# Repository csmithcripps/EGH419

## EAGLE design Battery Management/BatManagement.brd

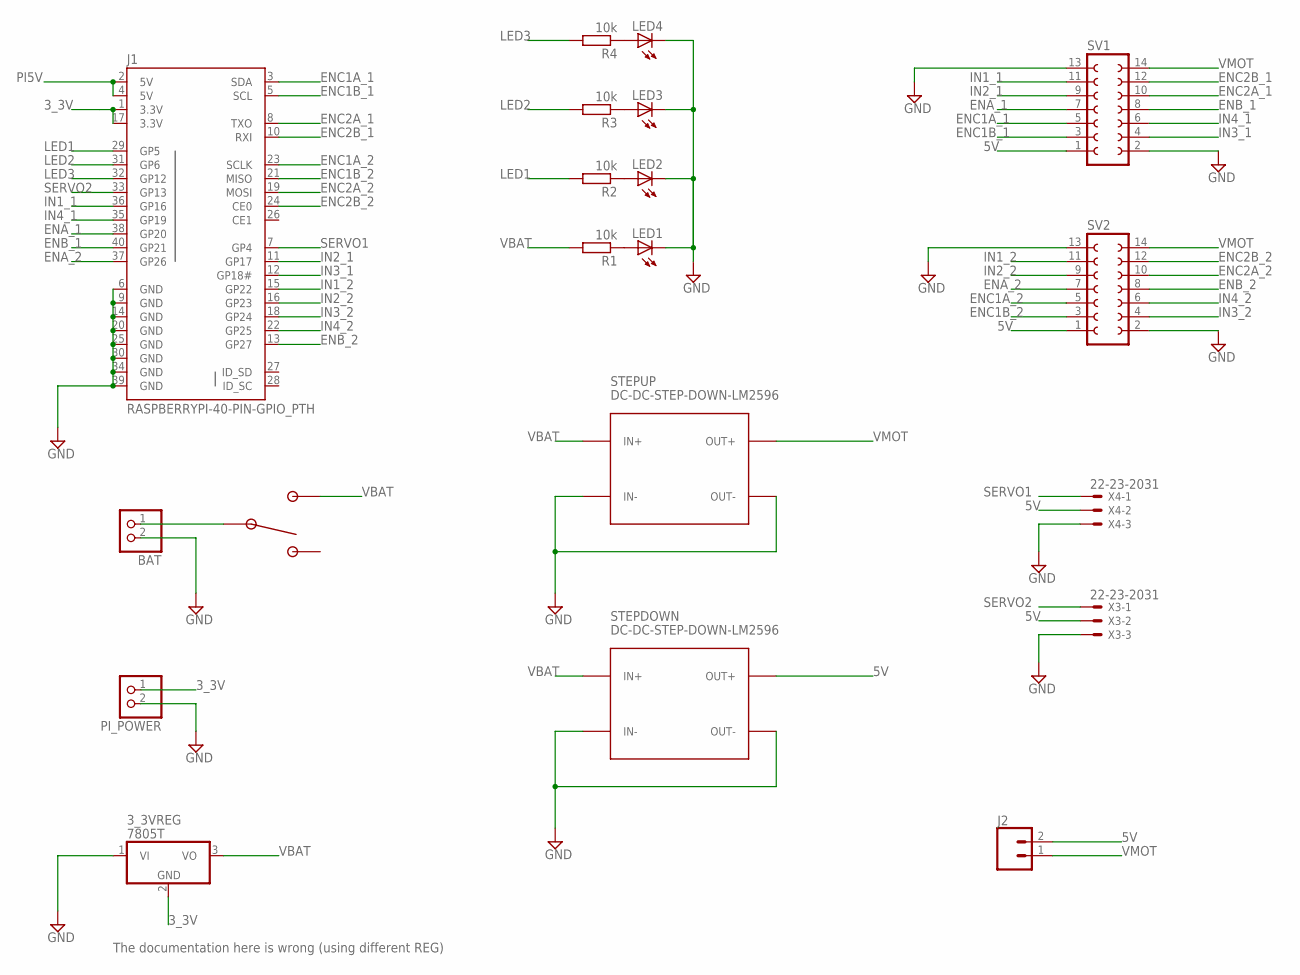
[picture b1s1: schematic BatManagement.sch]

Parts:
3_3VREG: 7805T; TO220H
BAT: JST_2PIN-THM; JST-PH-2-THM
J1: RASPBERRYPI-40-PIN-GPIO_PTH; 2X20_SHROUDED
J2: CONN_02; 1X02
LED1, LED2, LED3, LED4: LED5MM
PI_POWER: JST_2PIN-THM; JST-PH-2-THM
R1, R2, R3, R4: 10k; 0204/5
STEPDOWN: DC-DC-STEP-DOWN-LM2596
STEPUP: DC-DC-STEP-DOWN-LM2596
SV1, SV2: FE07-2
SW1: 100SP1T2B4M6QE; TOGGLE_RA
X3, X4: 22-23-2031

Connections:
3_3V: 3_3VREG.2 (GND), J1.1 (3.3V), J1.17 (3.3V), PI_POWER.1 (2)
5V: J2.2, STEPDOWN.OUT+, SV1.1, SV2.1, X3.2, X4.2
ENA_1: J1.38 (GP20), SV1.7
ENA_2: J1.37 (GP26), SV2.7
ENB_1: J1.40 (GP21), SV1.8
ENB_2: J1.13 (GP27), SV2.8
ENC1A_1: J1.3 (SDA), SV1.5
ENC1A_2: J1.23 (SCLK), SV2.5
ENC1B_1: J1.5 (SCL), SV1.3
ENC1B_2: J1.21 (MISO), SV2.3
ENC2A_1: J1.8 (TXO), SV1.10
ENC2A_2: J1.19 (MOSI), SV2.10
ENC2B_1: J1.10 (RXI), SV1.12
ENC2B_2: J1.24 (CE0), SV2.12
GND: 3_3VREG.1 (VI), BAT.2 (1), J1.6 (GND), J1.9 (GND), J1.14 (GND), J1.20 (GND), J1.25 (GND), J1.30 (GND), J1.34 (GND), J1.39 (GND), LED1.K (C), LED2.K (C), LED3.K (C), LED4.K (C), PI_POWER.2 (1), STEPDOWN.IN-, STEPDOWN.OUT-, STEPUP.IN-, STEPUP.OUT-, SV1.2, SV1.13, SV2.2, SV2.13, X3.3, X4.3
IN1_1: J1.36 (GP16), SV1.11
IN1_2: J1.15 (GP22), SV2.11
IN2_1: J1.11 (GP17), SV1.9
IN2_2: J1.16 (GP23), SV2.9
IN3_1: J1.12 (GP18#), SV1.4
IN3_2: J1.18 (GP24), SV2.4
IN4_1: J1.35 (GP19), SV1.6
IN4_2: J1.22 (GP25), SV2.6
LED1: J1.29 (GP5), R2.2
LED2: J1.31 (GP6), R3.2
LED3: J1.32 (GP12), R4.2
unnamed: LED1.A, R1.1
unnamed: LED2.A, R2.1
unnamed: LED3.A, R3.1
unnamed: LED4.A, R4.1
unnamed: BAT.1 (2), SW1.2 (COM)
PI5V: J1.2 (5V), J1.4 (5V)
SERVO1: J1.7 (GP4), X4.1
SERVO2: J1.33 (GP13), X3.1
VBAT: 3_3VREG.3 (VO), R1.2, STEPDOWN.IN+, STEPUP.IN+, SW1.1
VMOT: J2.1, STEPUP.OUT+, SV1.14, SV2.14

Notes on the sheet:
The documentation here is wrong (using different REG)

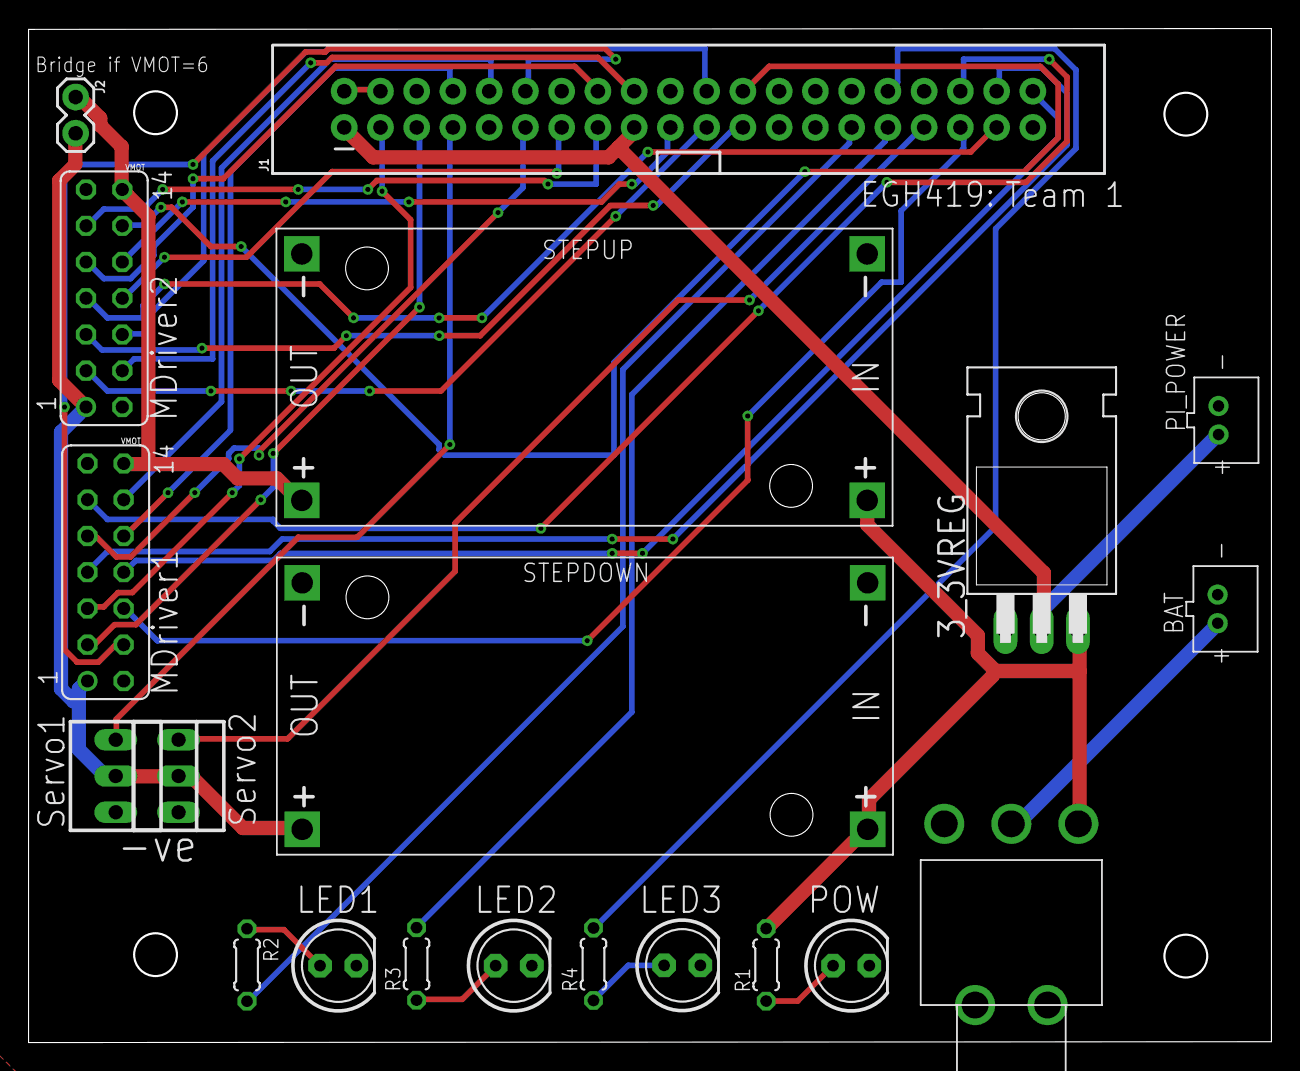
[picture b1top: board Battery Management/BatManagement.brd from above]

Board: 2 copper layers, 87.1 x 71.1 mm, 20 parts (0 on the bottom side), 36 nets.

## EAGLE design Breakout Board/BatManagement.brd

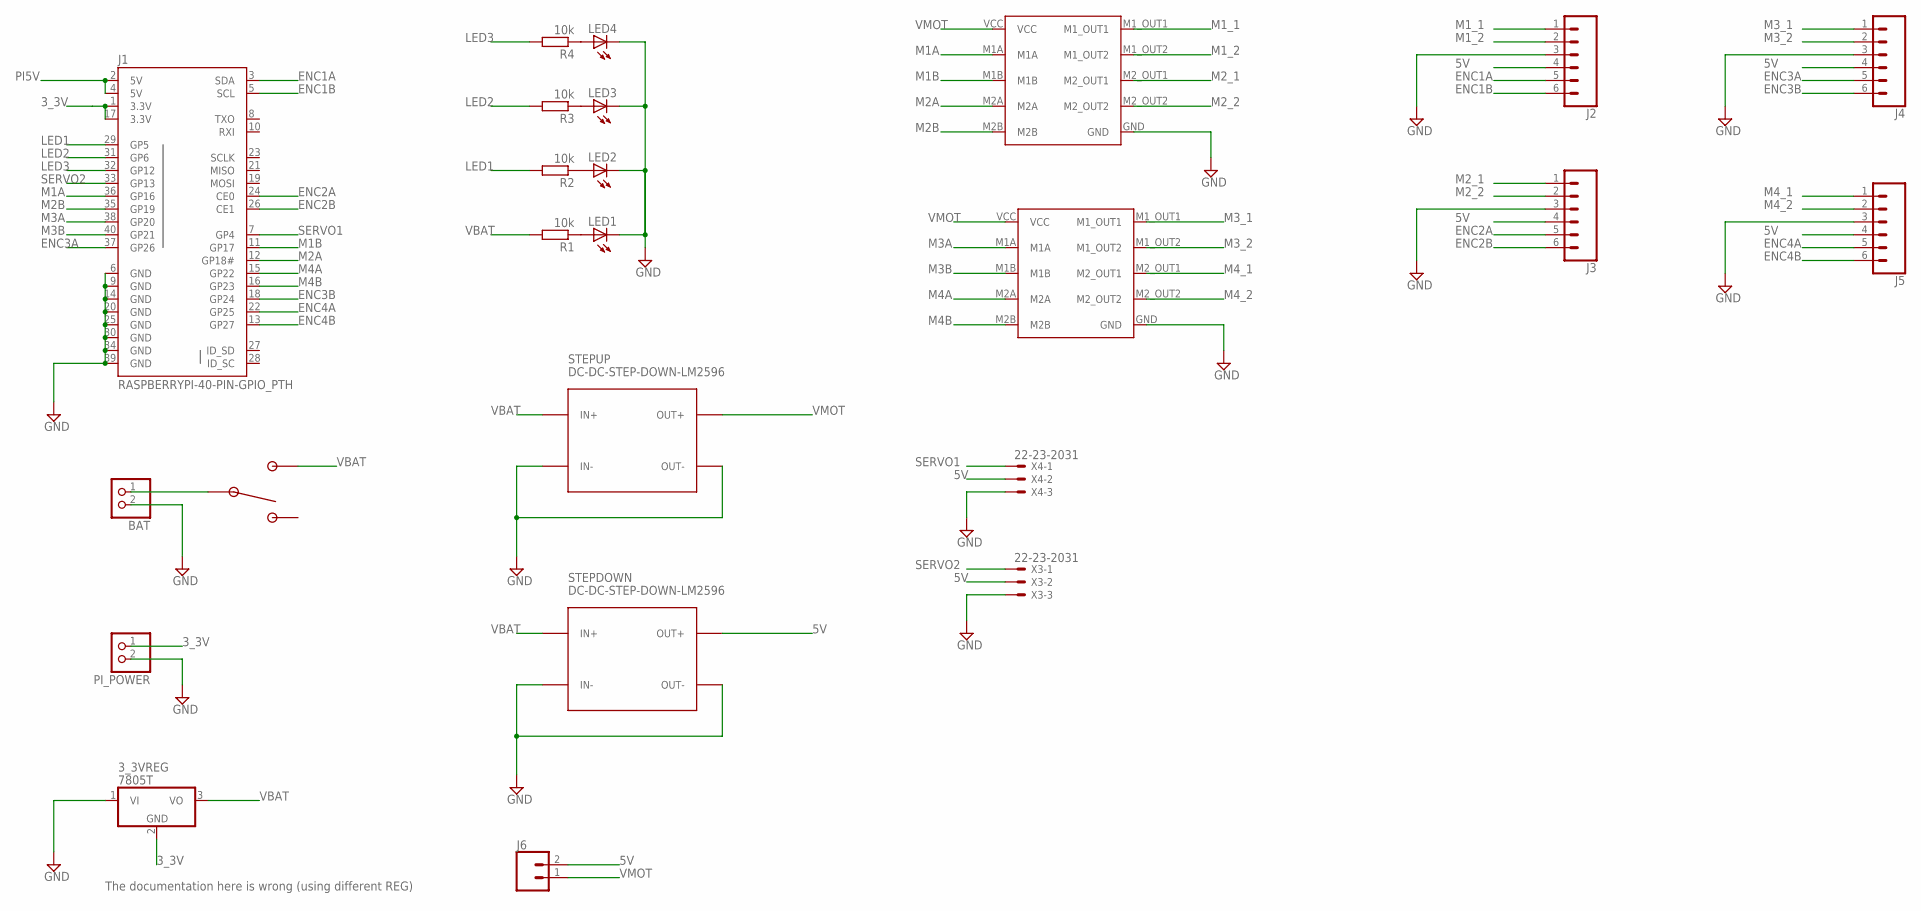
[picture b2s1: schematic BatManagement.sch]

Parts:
3_3VREG: 7805T; TO220H
BAT: JST_2PIN-THM; JST-PH-2-THM
J1: RASPBERRYPI-40-PIN-GPIO_PTH; 2X20_SHROUDED
J2, J3, J4, J5: CONN_06SILK_FEMALE_PTH; 1X06
J6: CONN_02; 1X02
LED1, LED2, LED3, LED4: LED5MM
MDRIVER1, MDRIVER2: LV8548MC_BOARD
PI_POWER: JST_2PIN-THM; JST-PH-2-THM
R1, R2, R3, R4: 10k; 0204/5
STEPDOWN: DC-DC-STEP-DOWN-LM2596
STEPUP: DC-DC-STEP-DOWN-LM2596
SW1: 100SP1T2B4M6QE; TOGGLE_RA
X3, X4: 22-23-2031

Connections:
3_3V: 3_3VREG.2 (GND), J1.1 (3.3V), J1.17 (3.3V), PI_POWER.1 (2)
5V: J2.4, J3.4, J4.4, J5.4, J6.2, STEPDOWN.OUT+, X3.2, X4.2
ENC1A: J1.3 (SDA), J2.5
ENC1B: J1.5 (SCL), J2.6
ENC2A: J1.24 (CE0), J3.5
ENC2B: J1.26 (CE1), J3.6
ENC3A: J1.37 (GP26), J4.5
ENC3B: J1.18 (GP24), J4.6
ENC4A: J1.22 (GP25), J5.5
ENC4B: J1.13 (GP27), J5.6
GND: 3_3VREG.1 (VI), BAT.2 (1), J1.6 (GND), J1.9 (GND), J1.14 (GND), J1.20 (GND), J1.25 (GND), J1.30 (GND), J1.34 (GND), J1.39 (GND), J2.3, J3.3, J4.3, J5.3, LED1.K (C), LED2.K (C), LED3.K (C), LED4.K (C), MDRIVER1.GND, MDRIVER2.GND, PI_POWER.2 (1), STEPDOWN.IN-, STEPDOWN.OUT-, STEPUP.IN-, STEPUP.OUT-, X3.3, X4.3
LED1: J1.29 (GP5), R2.2
LED2: J1.31 (GP6), R3.2
LED3: J1.32 (GP12), R4.2
M1A: J1.36 (GP16), MDRIVER1.M1A
M1B: J1.11 (GP17), MDRIVER1.M1B
M1_1: J2.1, MDRIVER1.M1_OUT1
M1_2: J2.2, MDRIVER1.M1_OUT2
M2A: J1.12 (GP18#), MDRIVER1.M2A
M2B: J1.35 (GP19), MDRIVER1.M2B
M2_1: J3.1, MDRIVER1.M2_OUT1
M2_2: J3.2, MDRIVER1.M2_OUT2
M3A: J1.38 (GP20), MDRIVER2.M1A
M3B: J1.40 (GP21), MDRIVER2.M1B
M3_1: J4.1, MDRIVER2.M1_OUT1
M3_2: J4.2, MDRIVER2.M1_OUT2
M4A: J1.15 (GP22), MDRIVER2.M2A
M4B: J1.16 (GP23), MDRIVER2.M2B
M4_1: J5.1, MDRIVER2.M2_OUT1
M4_2: J5.2, MDRIVER2.M2_OUT2
unnamed: LED1.A, R1.1
unnamed: LED2.A, R2.1
unnamed: LED3.A, R3.1
unnamed: LED4.A, R4.1
unnamed: BAT.1 (2), SW1.2 (COM)
PI5V: J1.2 (5V), J1.4 (5V)
SERVO1: J1.7 (GP4), X4.1
SERVO2: J1.33 (GP13), X3.1
VBAT: 3_3VREG.3 (VO), R1.2, STEPDOWN.IN+, STEPUP.IN+, SW1.1
VMOT: J6.1, MDRIVER1.VCC, MDRIVER2.VCC, STEPUP.OUT+

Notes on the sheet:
The documentation here is wrong (using different REG)

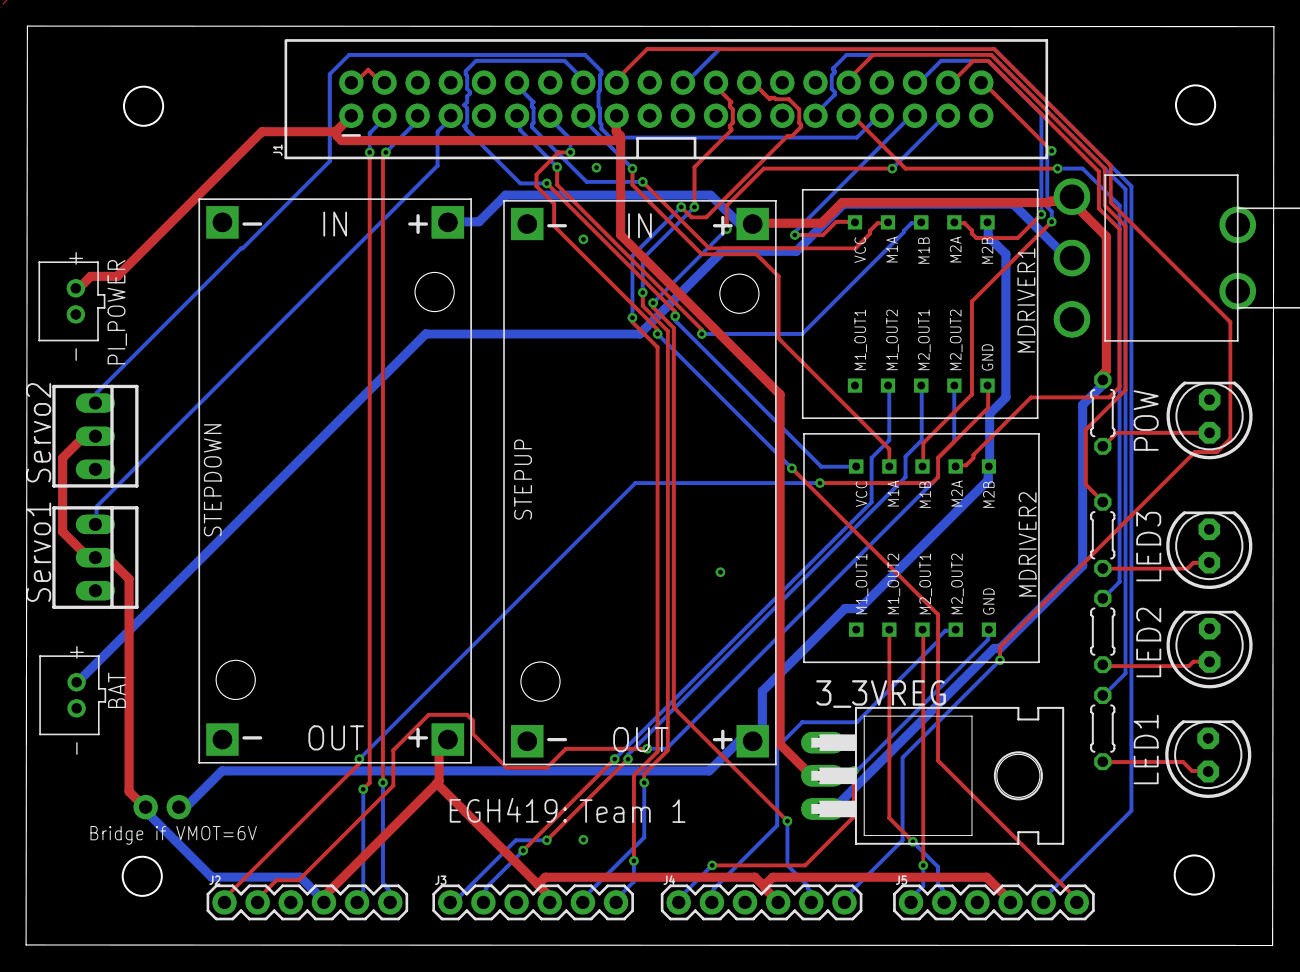
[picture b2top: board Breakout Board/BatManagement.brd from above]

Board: 2 copper layers, 95.6 x 70.4 mm, 24 parts (1 on the bottom side), 40 nets.

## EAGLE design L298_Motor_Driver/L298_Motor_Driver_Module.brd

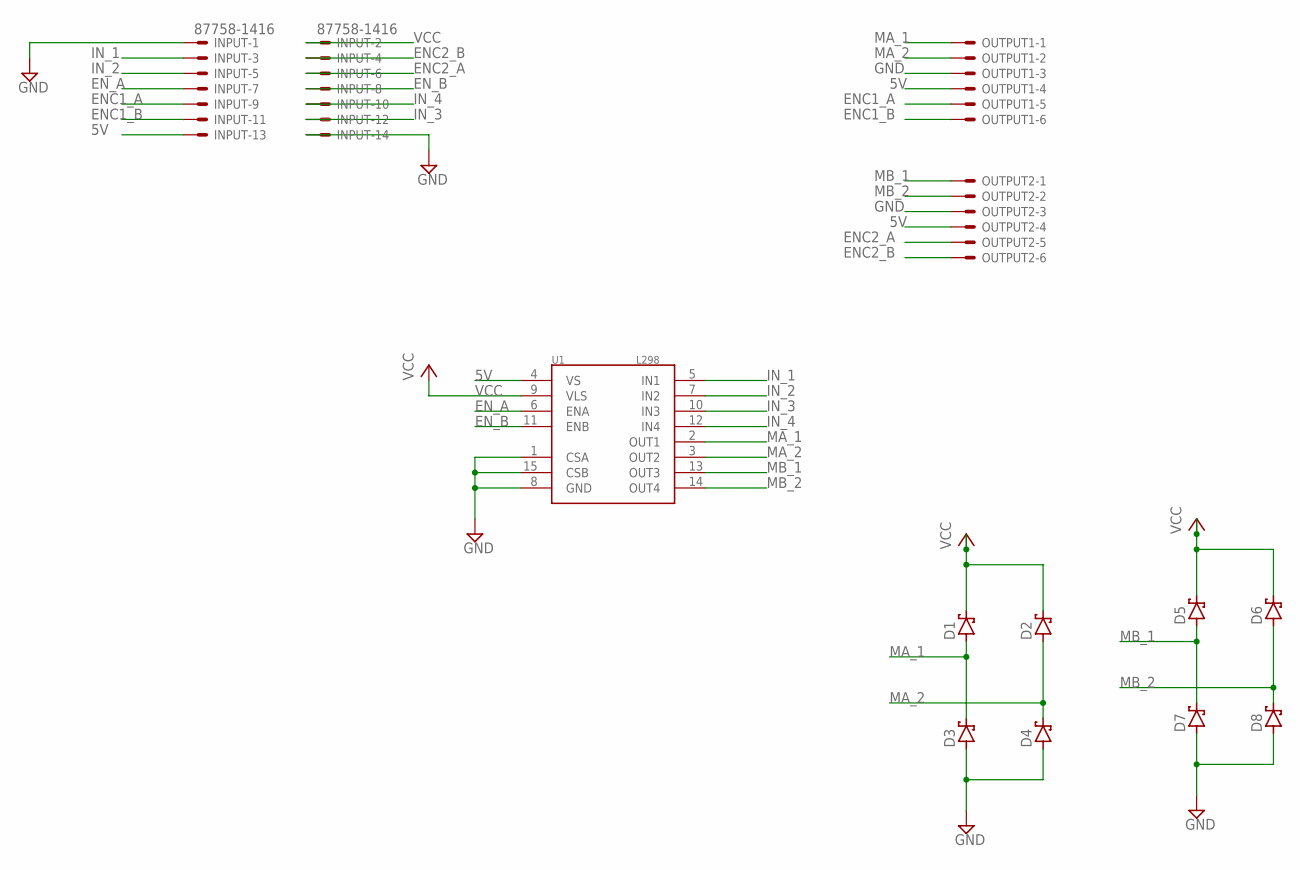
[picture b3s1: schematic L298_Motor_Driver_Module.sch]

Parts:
D1, D2, D3, D4, D5, D6, D7, D8: SCHOTTKY-DIODEDO35-7; DO35-7
INPUT: 87758-1416
OUTPUT1, OUTPUT2: 22-23-2061
U1: L298; MULTIWATT15

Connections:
5V: INPUT.13, OUTPUT1.4, OUTPUT2.4, U1.4 (VS)
ENC1_A: INPUT.9, OUTPUT1.5
ENC1_B: INPUT.11, OUTPUT1.6
ENC2_A: INPUT.6, OUTPUT2.5
ENC2_B: INPUT.4, OUTPUT2.6
EN_A: INPUT.7, U1.6 (ENA)
EN_B: INPUT.8, U1.11 (ENB)
GND: D3.A, D4.A, D7.A, D8.A, INPUT.1, INPUT.14, OUTPUT1.3, OUTPUT2.3, U1.1 (CSA), U1.8 (GND), U1.15 (CSB)
IN_1: INPUT.3, U1.5 (IN1)
IN_2: INPUT.5, U1.7 (IN2)
IN_3: INPUT.12, U1.10 (IN3)
IN_4: INPUT.10, U1.12 (IN4)
MA_1: D1.A, D3.C, OUTPUT1.1, U1.2 (OUT1)
MA_2: D2.A, D4.C, OUTPUT1.2, U1.3 (OUT2)
MB_1: D5.A, D7.C, OUTPUT2.1, U1.13 (OUT3)
MB_2: D6.A, D8.C, OUTPUT2.2, U1.14 (OUT4)
VCC: D1.C, D2.C, D5.C, D6.C, INPUT.2, U1.9 (VLS)

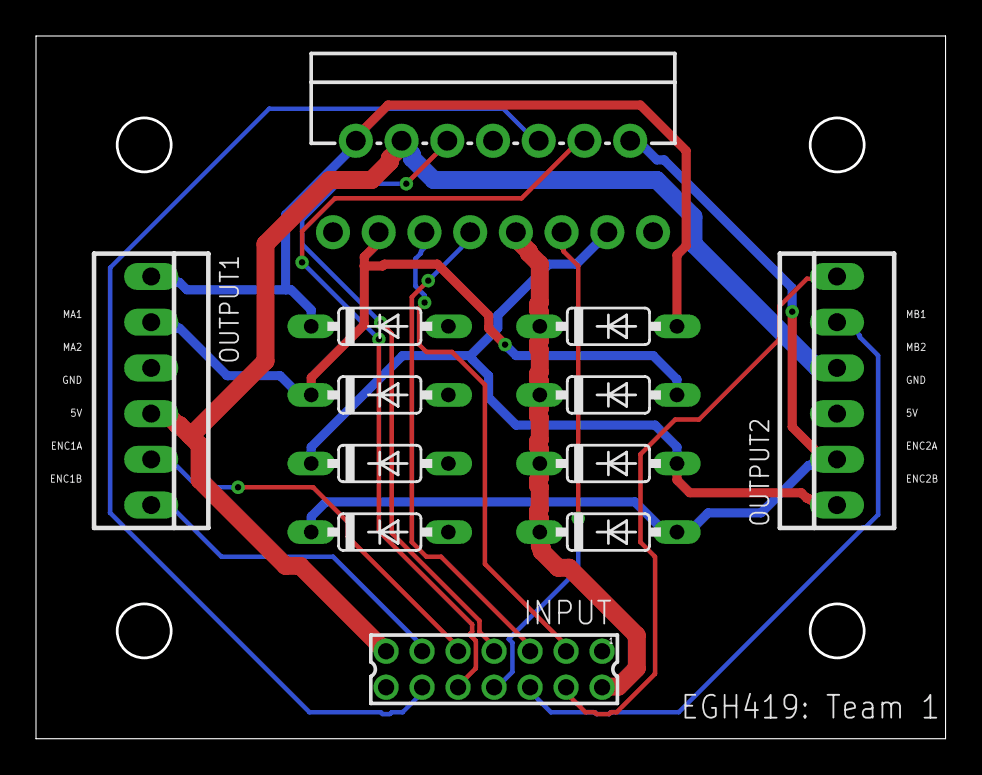
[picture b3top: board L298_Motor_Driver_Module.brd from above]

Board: 2 copper layers, 50.5 x 39.0 mm, 12 parts (0 on the bottom side), 17 nets.

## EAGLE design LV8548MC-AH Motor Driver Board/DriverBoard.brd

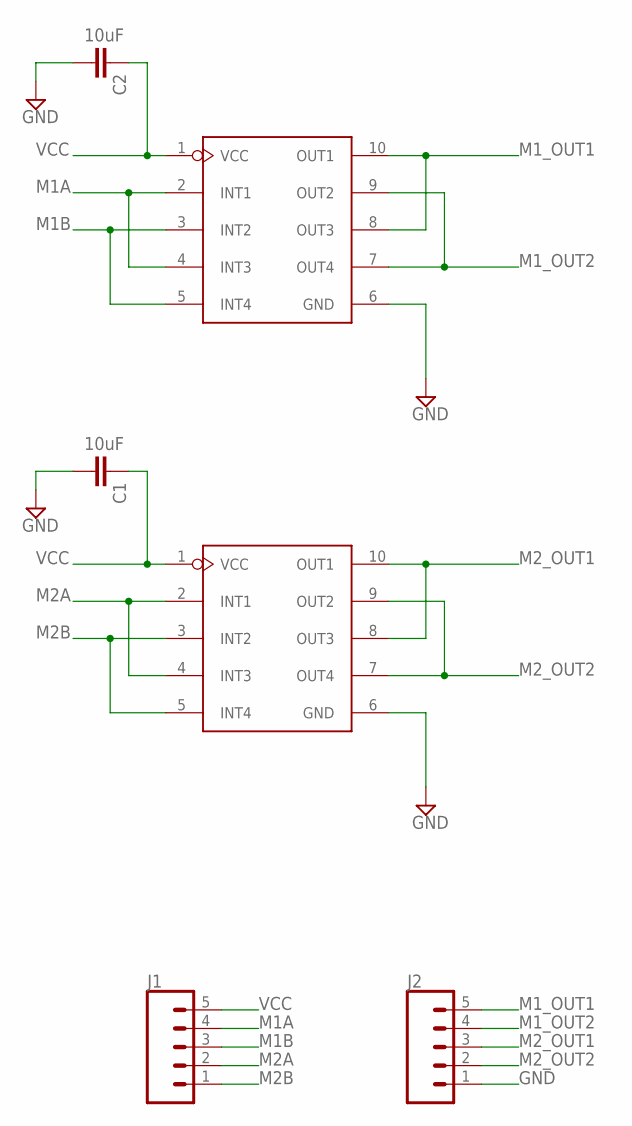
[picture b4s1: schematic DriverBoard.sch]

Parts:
C1, C2: 10uF; C0805
J1, J2: CONN_05; 1X05
U1, U2: DRIVER-LV8548MC-AH(SOIC10); SOIC10-1.0-5X4MM

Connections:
GND: C1.2, C2.2, J2.1, U1.6 (GND), U2.6 (GND)
M1A: J1.4, U2.2 (INT1), U2.4 (INT3)
M1B: J1.3, U2.3 (INT2), U2.5 (INT4)
M1_OUT1: J2.5, U2.8 (OUT3), U2.10 (OUT1)
M1_OUT2: J2.4, U2.7 (OUT4), U2.9 (OUT2)
M2A: J1.2, U1.2 (INT1), U1.4 (INT3)
M2B: J1.1, U1.3 (INT2), U1.5 (INT4)
M2_OUT1: J2.3, U1.8 (OUT3), U1.10 (OUT1)
M2_OUT2: J2.2, U1.7 (OUT4), U1.9 (OUT2)
VCC: C1.1, C2.1, J1.5, U1.1 (VCC), U2.1 (VCC)

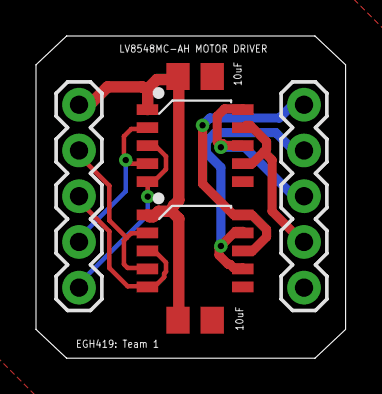
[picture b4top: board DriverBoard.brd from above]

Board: 2 copper layers, 17.2 x 17.9 mm, 6 parts (0 on the bottom side), 10 nets.

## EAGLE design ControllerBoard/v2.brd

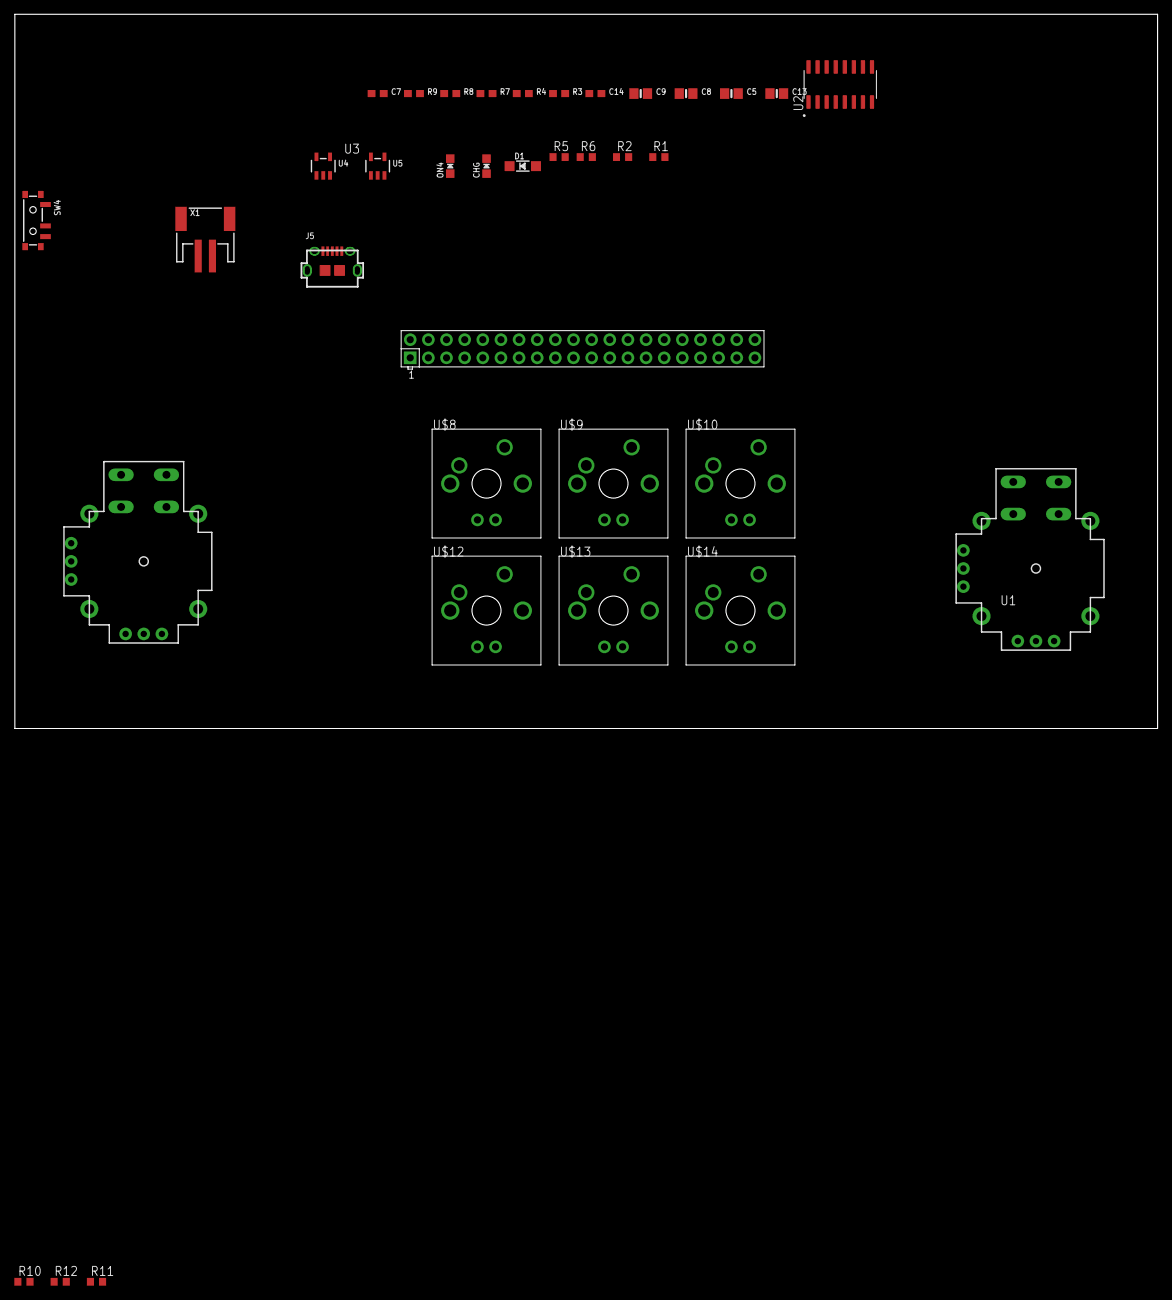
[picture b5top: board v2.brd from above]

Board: 2 copper layers, 160.0 x 100.0 mm, 36 parts (0 on the bottom side), 25 nets, no tracks yet.

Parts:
C5, C8, C9: 10µF; 0805-NO
C7, C14: 1uF; 0603-NO
C13: 10uF; 0805-NO
CHG: ORANGE; CHIPLED_0805_NOOUTLINE
D1: MBR120; SOD-123
J5: U-F-M5DD-Y-L; MICRO-SMD
ON4: GREEN; CHIPLED_0805_NOOUTLINE
R1, R2, R6, R10, R11, R12: 10k; R0603
R3: 1K; 0603-NO
R4, R9: 100k; 0603-NO
R5: 1k; R0603
R7: 100K; 0603-NO
R8: 10K\; 0603-NO
SW4: SPDT_SMT_SSSS811101
U1, U3: JOYSTICKPTH; JOYSTICK
U2: MCP3008-I/SL; SOIC127P600X175-16N
U4: SPX3819-3.3; SOT23-5
U5: MCP73831T-2ACI/OT; SOT23-5
U$1: RPI-ZERO; RASPBERRYPI_BASTELSTUBE_V13_RASPI_BOARD_B+_FULL
U$8, U$9, U$10, U$12, U$13, U$14: CHERRY-MX-LED
X1: JSTPH; JSTPH2

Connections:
3.3V: C7.1, C8.1, C13.1, ON4.A, R1.2, R2.2, R6.2, R10.2, R11.2, R12.2, U1.B1A, U1.H1, U1.V1, U2.15, U2.16, U3.B1A, U3.H1, U3.V1, U4.5
BATTERY_SENSE: R4.2, R7.1
BTN_A: R6.1, U$1.29, U$8.SW1
BTN_B: R1.1, U$1.31, U$9.SW1
BTN_C: R2.1, U$1.33, U$10.SW1
BTN_D: R10.1, U$12.SW1
BTN_E: R11.1, U$13.SW1
BTN_F: R12.1, U$14.SW1
CE0: U2.10, U$1.24
EN: R9.2, U4.3
GND: C5.2, C7.2, C8.2, C9.2, C13.2, C14.2, J5.GND, J5.S1, J5.S1@1, J5.S1@2, J5.S2, J5.S2@1, J5.S2@2, J5.S3, J5.S3@1, J5.S3@2, J5.S4, J5.S4@1, J5.S4@2, J5.S5, J5.S6, R5.2, R7.2, R8.2, U1.H3, U1.V3, U2.9, U2.14, U3.H3, U3.V3, U4.2, U5.2, U$8.SW2, U$9.SW2, U$10.SW2, U$12.SW2, U$13.SW2, U$14.SW2, X1.1
H1: U2.2, U3.H2
H2: U1.H2, U2.4
MISO: U2.12, U$1.21
MOSI: U2.11, U$1.19
unnamed: CHG.C, R3.1
unnamed: SW4.C, X1.2
unnamed: R3.2, U5.1
unnamed: R8.1, U5.5
unnamed: ON4.C, R5.1
SCLK: U2.13, U$1.23
V1: U2.1, U3.V2
V2: U1.V2, U2.3
VBAT: C9.1, D1.A, R4.1, SW4.B, U5.3
VBUS: C5.1, CHG.A, D1.C, J5.VBUS, R9.1, U4.1, U5.4

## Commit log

2021-03-23 Added Project for controller PCB
2021-03-23 Do the thing
2021-03-30 Boards ready for review
2021-03-30 Added Breakout Board2
2021-03-31 check
2021-03-31 Added jumper for 6V motors
2021-03-31 Added jumper to breakout2
2021-03-31 added new bb to zip
2021-03-31 Changed to standard header for mdriver connection
2021-04-07 Reshaped Board

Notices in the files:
parts and their libraries:
SparkFun-Connectors: Licensing: Creative Commons ShareAlike 4.0 International - https://creativecommons.org/licenses/by-sa/4.0
diy-modules: Released under the Creative Commons Attribution 4.0 International License: http://creativecommons.org/licenses/by/4.0
